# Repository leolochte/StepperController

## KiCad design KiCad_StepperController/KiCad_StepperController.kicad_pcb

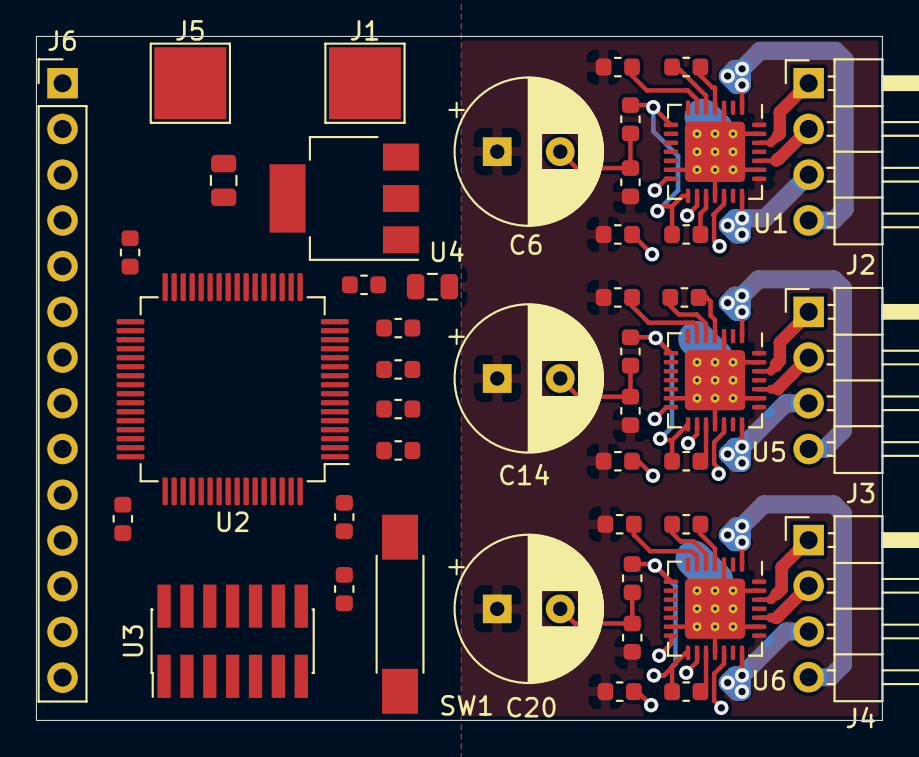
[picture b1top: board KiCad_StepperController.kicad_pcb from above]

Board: 2 copper layers, 47.0 x 38.0 mm, 45 parts (0 on the bottom side), 56 nets.

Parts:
C1, C8, C15: 2.2 uF; C_0603_1608Metric
C2, C9, C16: 22 nF; C_0603_1608Metric
C3, C4, C5, C11, C12, C13, C17, C18, C19, C21, C22, C23, C24, C27: 100 nF; C_0603_1608Metric
C6, C14, C20: 100 uF; CP_Radial_D8.0mm_P3.50mm
C7, C10: 10 uF; C_0805_2012Metric
C25, C28: 1 uF; C_0603_1608Metric
C26: 4.7 uF; C_0603_1608Metric
J1, J5: Conn_01x01; TestPoint_Pad_4.0x4.0mm
J2, J3, J4: M1; PinHeader_1x04_P2.54mm_Horizontal
J6: Conn_01x14; PinHeader_1x14_P2.54mm_Vertical
R1, R2, R3, R4: 10 kOhm; R_0603_1608Metric
SW1: SW_Push; SW_SPST_REED_CT05-XXXX-G1
U1, U5, U6: TMC2208; QFN-28-1EP_5x5mm_P0.5mm_EP3.35x3.35mm_ThermalVias
U2: STM32L151RCTx; LQFP-64_10x10mm_P0.5mm
U3: STLINK-V3MINI; PinHeader_2x07_P1.27mm_Vertical_SMD
U4: AMS1117-3.3; SOT-223-3_TabPin2

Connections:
+3V3: C10.1, C21.1, C22.1, C23.1, C24.1, C26.1, C27.1, C28.1, R4.2, U2.13, U2.19, U2.32, U2.48, U2.64, U3.3, U4.2
GND: C1.2, C4.2, C5.2, C6.2, C7.2, C8.2, C10.2, C12.2, C13.2, C14.2, C15.2, C18.2, C19.2, C20.2, C21.2, C22.2, C23.2, C24.2, C25.2, C26.2, C27.2, C28.2, J5.1, SW1.1, U1.3, U1.13, U1.18, U1.23, U1.27, U1.29, U2.12, U2.18, U2.31, U2.47, U2.60, U2.63, U3.5, U3.7, U3.11, U4.1, U5.3, U5.13, U5.18, U5.23, U5.27, U5.29, U6.3, U6.13, U6.18, U6.23, U6.27, U6.29
M1_DIR: U1.19, U2.27
M1_STEP: U1.16, U2.26
M2_DIR: U2.55, U5.19
M2_STEP: U2.28, U5.16
M3_DIR: U2.57, U6.19
M3_STEP: U2.56, U6.16
Mx_UART: U1.14, U2.29, U5.14, U6.14
NRST: C25.1, R4.1, SW1.2, U2.7, U3.12
unnamed: C1.1, R1.2, U1.8, U1.15
unnamed: C2.1, U1.4
unnamed: C2.2, U1.5
unnamed: C3.1, U1.6
unnamed: C8.1, R2.2, U5.8, U5.15
unnamed: C9.1, U5.4
unnamed: C9.2, U5.5
unnamed: C11.1, U5.6
unnamed: C15.1, R3.2, U6.8, U6.15
unnamed: C16.1, U6.4
unnamed: C16.2, U6.5
unnamed: C17.1, U6.6
unnamed: J2.1, U1.26
unnamed: J2.2, U1.24
unnamed: J2.3, U1.21
unnamed: J2.4, U1.1
unnamed: J3.1, U5.26
unnamed: J3.2, U5.24
unnamed: J3.3, U5.21
unnamed: J3.4, U5.1
unnamed: J4.1, U6.26
unnamed: J4.2, U6.24
unnamed: J4.3, U6.21
unnamed: J4.4, U6.1
unnamed: R1.1, U1.17
unnamed: R2.1, U5.17
unnamed: R3.1, U6.17
PA0: J6.1, U2.14
PA1: J6.2, U2.15
PA2: J6.3, U2.16
PA3: J6.4, U2.17
PA4: J6.5, U2.20
PA5: J6.6, U2.21
PA6: J6.7, U2.22
PA7: J6.8, U2.23
PA8: J6.9, U2.41
PA9: J6.10, U2.42
PA10: J6.11, U2.43
PA11: J6.12, U2.44
PB8: J6.13, U2.61
PB9: J6.14, U2.62
SWCLK: U2.49, U3.6
SWDIO: U2.46, U3.4
T_VCP_RX: U2.59, U3.13
T_VCP_TX: U2.58, U3.14
VCC: C3.2, C4.1, C5.1, C6.1, C7.1, C11.2, C12.1, C13.1, C14.1, C17.2, C18.1, C19.1, C20.1, J1.1, U1.22, U1.28, U4.3, U5.22, U5.28, U6.22, U6.28

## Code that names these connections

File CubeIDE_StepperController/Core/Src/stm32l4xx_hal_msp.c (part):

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
    __HAL_RCC_GPIOA_CLK_ENABLE();
    /**I2C1 GPIO Configuration
    PA9     ------> I2C1_SCL
    PA10     ------> I2C1_SDA
    */
    GPIO_InitStruct.Pin = GPIO_PIN_9|GPIO_PIN_10;
    GPIO_InitStruct.Mode = GPIO_MODE_AF_OD;
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    __HAL_RCC_I2C1_CLK_DISABLE();

    /**I2C1 GPIO Configuration
    PA9     ------> I2C1_SCL
    PA10     ------> I2C1_SDA
    */
    HAL_GPIO_DeInit(GPIOA, GPIO_PIN_9);

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
    __HAL_RCC_GPIOA_CLK_ENABLE();
    /**TIM2 GPIO Configuration
    PA0     ------> TIM2_CH1
    PA1     ------> TIM2_CH2
    */
    GPIO_InitStruct.Pin = RE_CLK_Pin|RE_DT_Pin;
    GPIO_InitStruct.Mode = GPIO_MODE_AF_PP;
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    __HAL_RCC_TIM2_CLK_DISABLE();

    /**TIM2 GPIO Configuration
    PA0     ------> TIM2_CH1
    PA1     ------> TIM2_CH2
    */
    HAL_GPIO_DeInit(GPIOA, RE_CLK_Pin|RE_DT_Pin);

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
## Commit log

2021-04-04 First Working Version
    Controlling Stepper with speed, acc. and time
2021-04-04 DMA running constantly
2021-04-04 removed getadcvalues
2021-04-04 Switched to structs for steppers
    This allows for n steppers to run in sync
2021-04-05 moving stepper code to stepper.c and stepper.h
    does not compile, htim6 undeclared
2021-04-05 Fixed stepper speed and cleanup
    Fixed math so the Steppers respond consistently across time inputs, but the time input is now inverse. Handle with care.
2021-04-06 Fixed inverted time input and math mistake
    Fully functional, slight time overrun during longer durations
2021-04-06 Changed repo structure
2021-04-06 Changed repo structure
    Correct naming of project, possibility to create a workspace from repo folder and still possible to open project
2021-04-08 Switched to typedef steppers, asynchronous stepper movements
2021-04-08 Added array for movements
2021-04-08 Adjusted stepper movements for better demo
2021-06-02 started kicad project
2021-06-03 started layout
2021-06-17 changed formfactor

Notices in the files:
CubeIDE_StepperController/Core/Src/stm32l4xx_hal_msp.c:
© Copyright (c) 2021 STMicroelectronics.
All rights reserved.
This software component is licensed by ST under BSD 3-Clause license,
the "License"; You may not use this file except in compliance with the
License. You may obtain a copy of the License at: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
(C) COPYRIGHT STMicroelectronics *****END OF FILE
